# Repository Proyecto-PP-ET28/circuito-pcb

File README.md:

<picture>
  <source media="(prefers-color-scheme: dark)" srcset="https://i.imgur.com/kT6ZOKA.png">
  
</picture>

# Hardware
> Este repo contiene el diseño del circuito esquemático y circuito impreso correspondientes al proyecto ESIMA.

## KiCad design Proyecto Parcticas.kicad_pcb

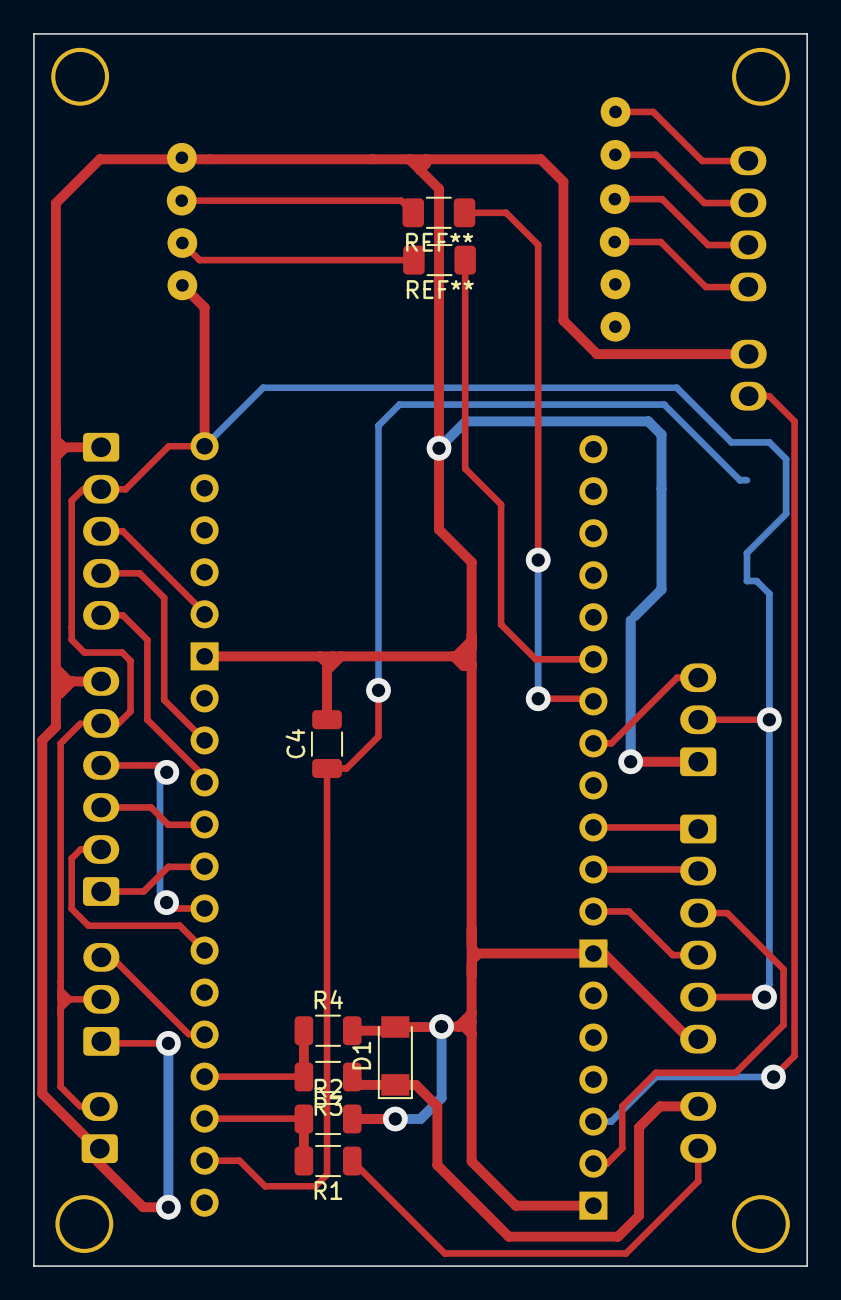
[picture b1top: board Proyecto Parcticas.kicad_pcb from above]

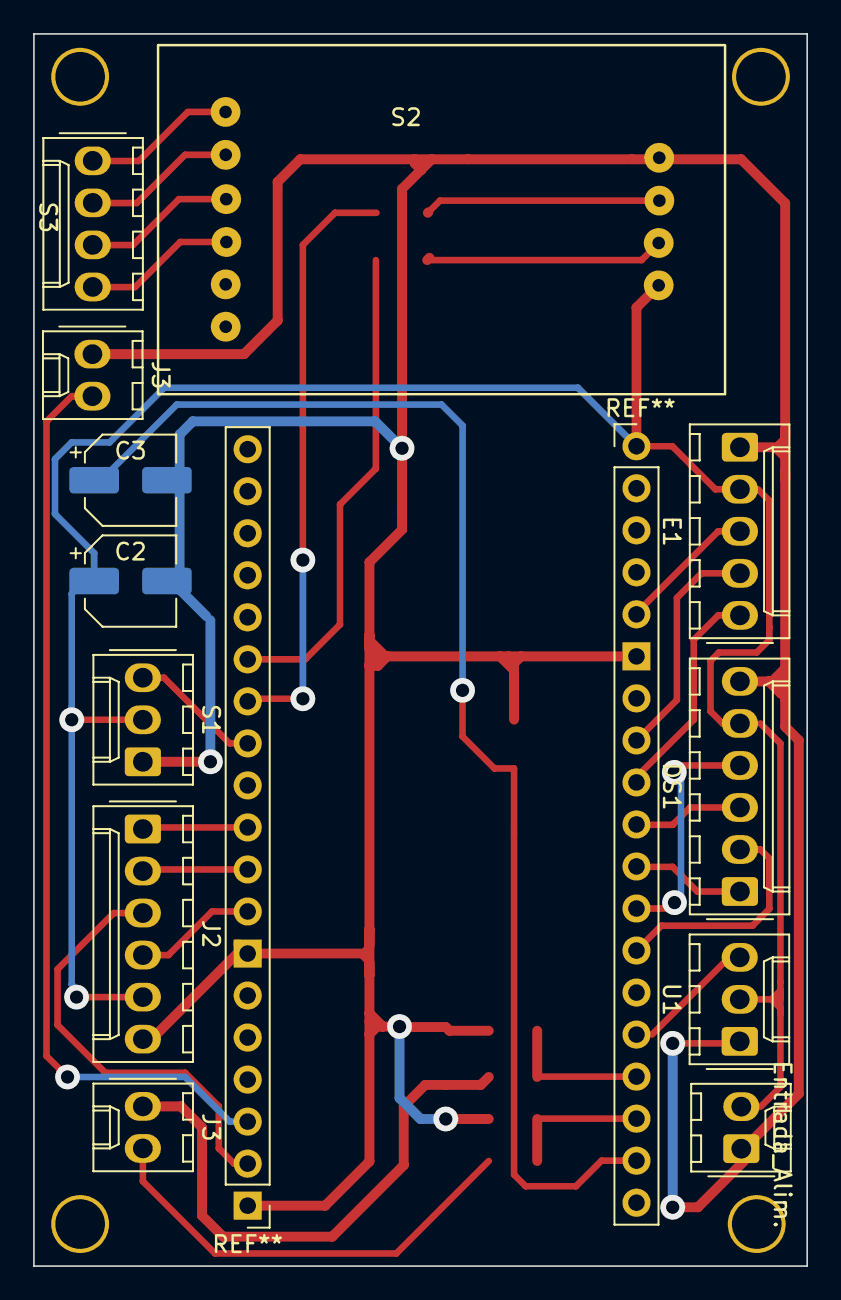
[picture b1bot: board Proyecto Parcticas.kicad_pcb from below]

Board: 2 copper layers, 46.7 x 74.5 mm, 18 parts (12 on the bottom side), 11 nets.

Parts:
C2: 220uF; CP_Elec_5x5.4
C3: 10uF; CP_Elec_5x5.4
C4: 100nF; C_1206_3216Metric
D1: 1N4752; D_MiniMELF
DS1: Molex_KK-254_AE-6410-06A_1x06_P2.54mm_Vertical
E1: Encoder_rotativo; Molex_KK-254_AE-6410-05A_1x05_P2.54mm_Vertical
Entrada_Alim.: StepUp 5v; Molex_KK-254_AE-6410-02A_1x02_P2.54mm_Vertical
J2: Molex_KK-254_AE-6410-06A_1x06_P2.54mm_Vertical
J3, J3#2: Baterias; Molex_KK-254_AE-6410-02A_1x02_P2.54mm_Vertical
R1, R2, R4: 100k; R_1206_3216Metric
R3: 1M; R_1206_3216Metric
S1: Sensor_Infrarrojo; Molex_KK-254_AE-6410-03A_1x03_P2.54mm_Vertical
S2: XH711; HX711
S3: Sensor_de_Carga; Molex_KK-254_AE-6410-04A_1x04_P2.54mm_Vertical
U1: Sensor_de_corriente_ACS758LCB; Molex_KK-254_AE-6410-03A_1x03_P2.54mm_Vertical

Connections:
BAT+_EXT: R3.2, R4.1
BAT+_INT: R1.2, R2.1
BAText+: D1.1 (K), R3.1
BATint+: J3.2, R1.1
EN: C3.1, C4.1
GND: C2.2, C3.2, C4.2, D1.2 (A), DS1.6, E1.5, Entrada_Alim..1 (VIN+), J2.6, R2.2, R4.2, S1.3, S2.5 (GND), U1.1
unnamed: S2.1 (A+), S3.4
unnamed: S2.2 (A-), S3.3
unnamed: S2.3 (E+), S3.1
unnamed: S2.4 (E-), S3.2
VCC: C2.1, DS1.5, E1.4, Entrada_Alim..2 (VIN_), J2.5, S1.2, S2.8 (VCC), U1.2

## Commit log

2022-04-07 Estructura base de KiCad
2022-04-14 Creación de componentes
2022-06-15 Ultima versión
2022-08-12 Ultima version
2022-08-30 Ultima super mejorada
2022-09-03 <Arreglo divisor de tensión baterias>
2022-09-03 <Agregué el PWM>
2022-09-03 <Step agregado>
2022-09-04 <Revisión PCB y STEP>
